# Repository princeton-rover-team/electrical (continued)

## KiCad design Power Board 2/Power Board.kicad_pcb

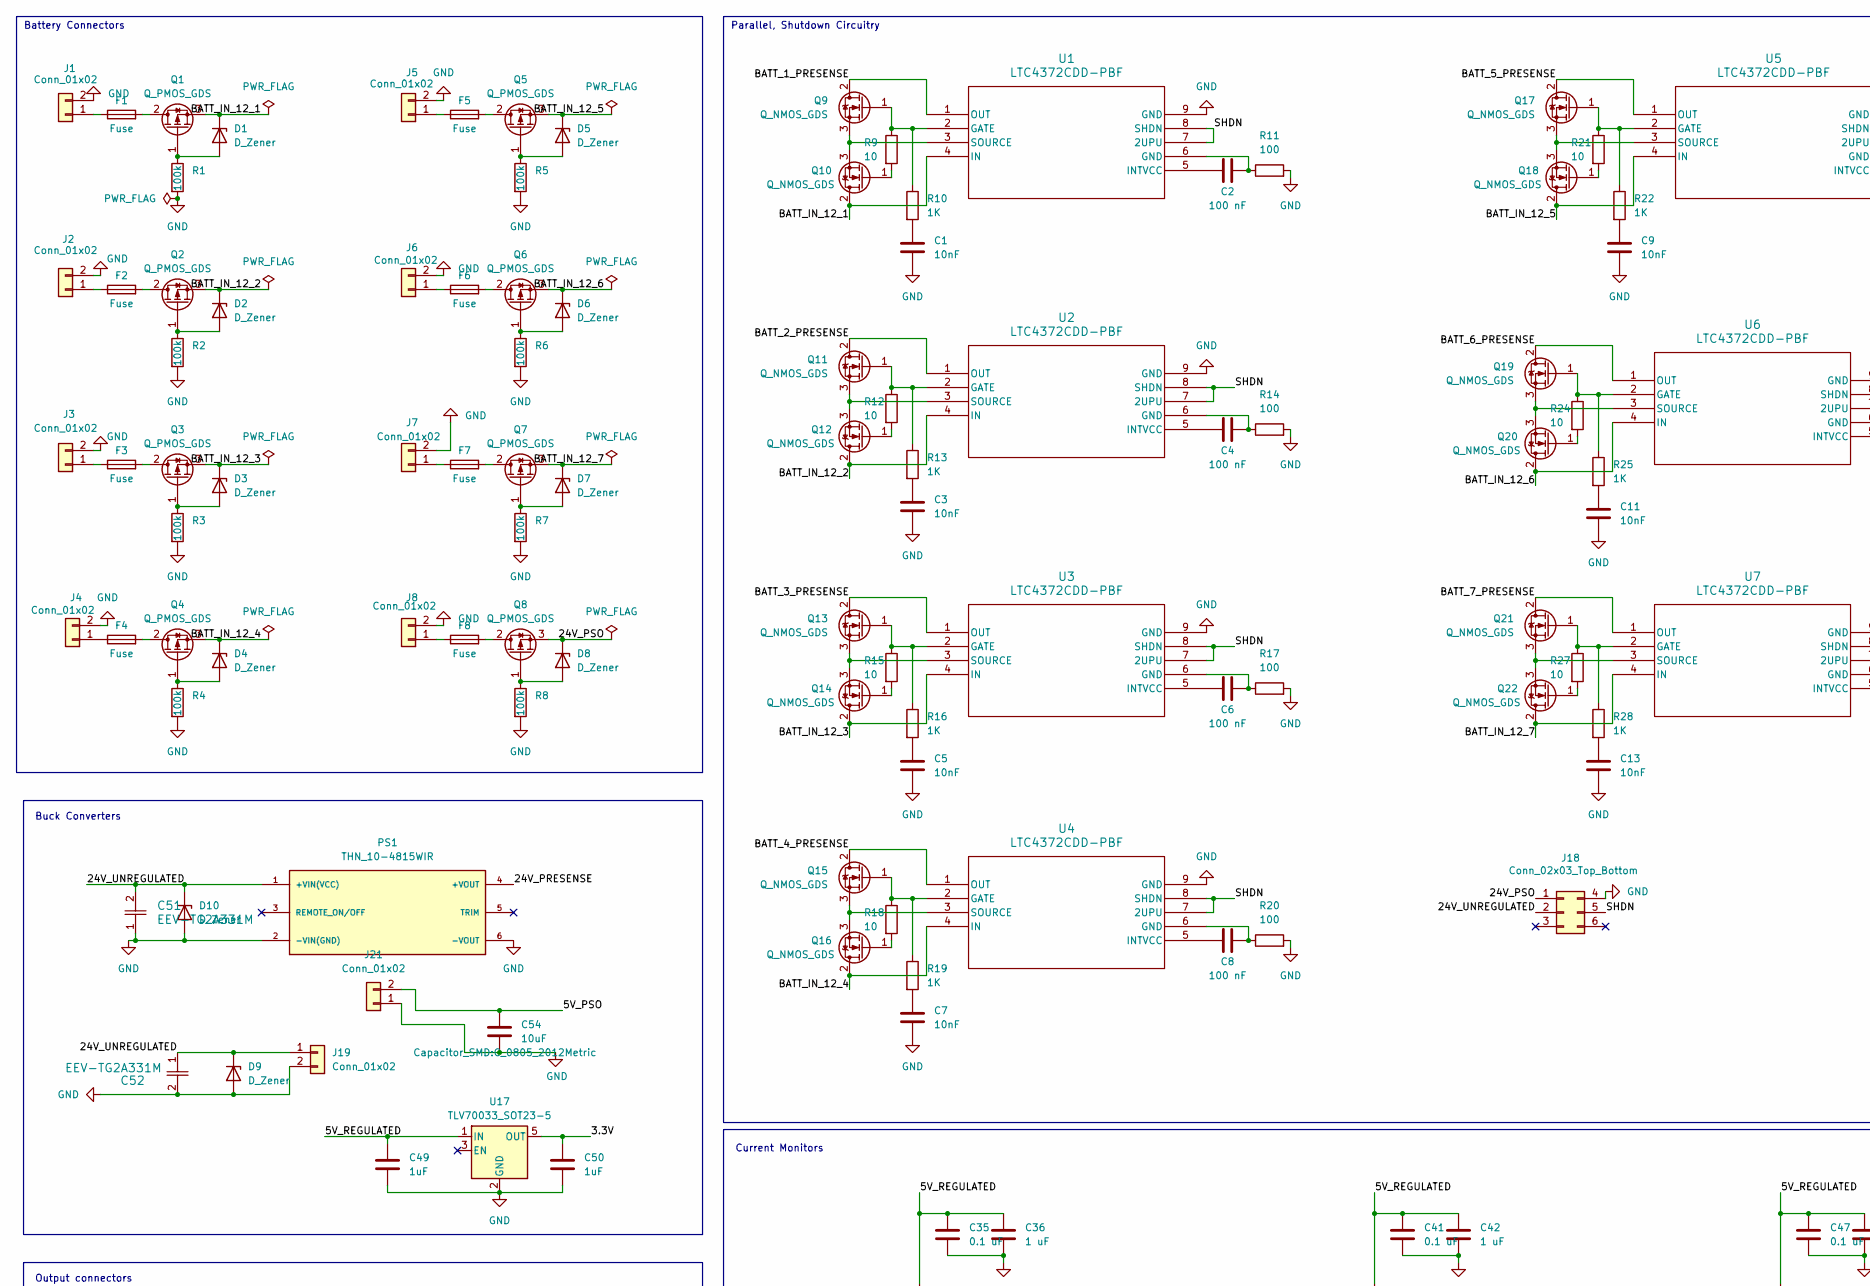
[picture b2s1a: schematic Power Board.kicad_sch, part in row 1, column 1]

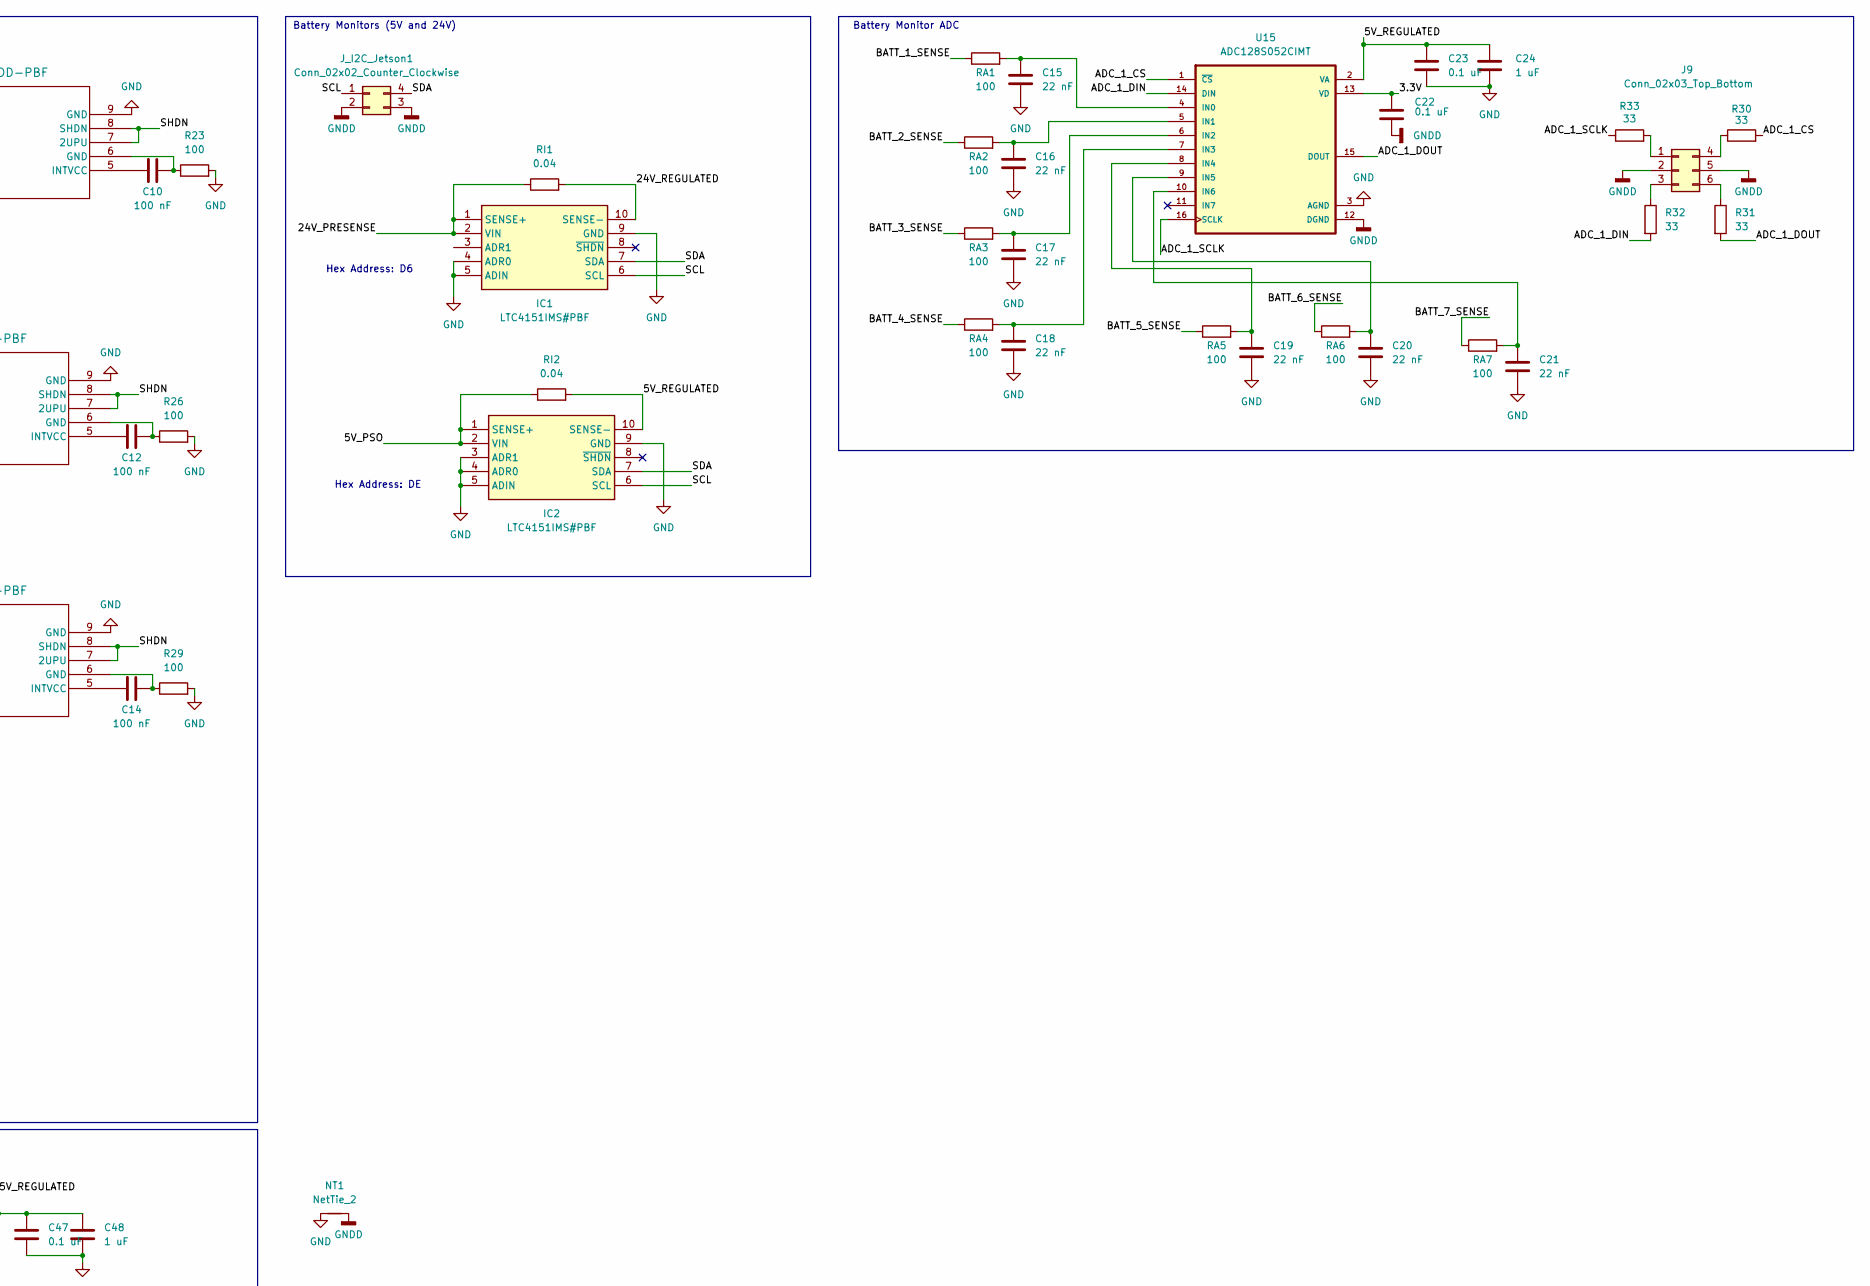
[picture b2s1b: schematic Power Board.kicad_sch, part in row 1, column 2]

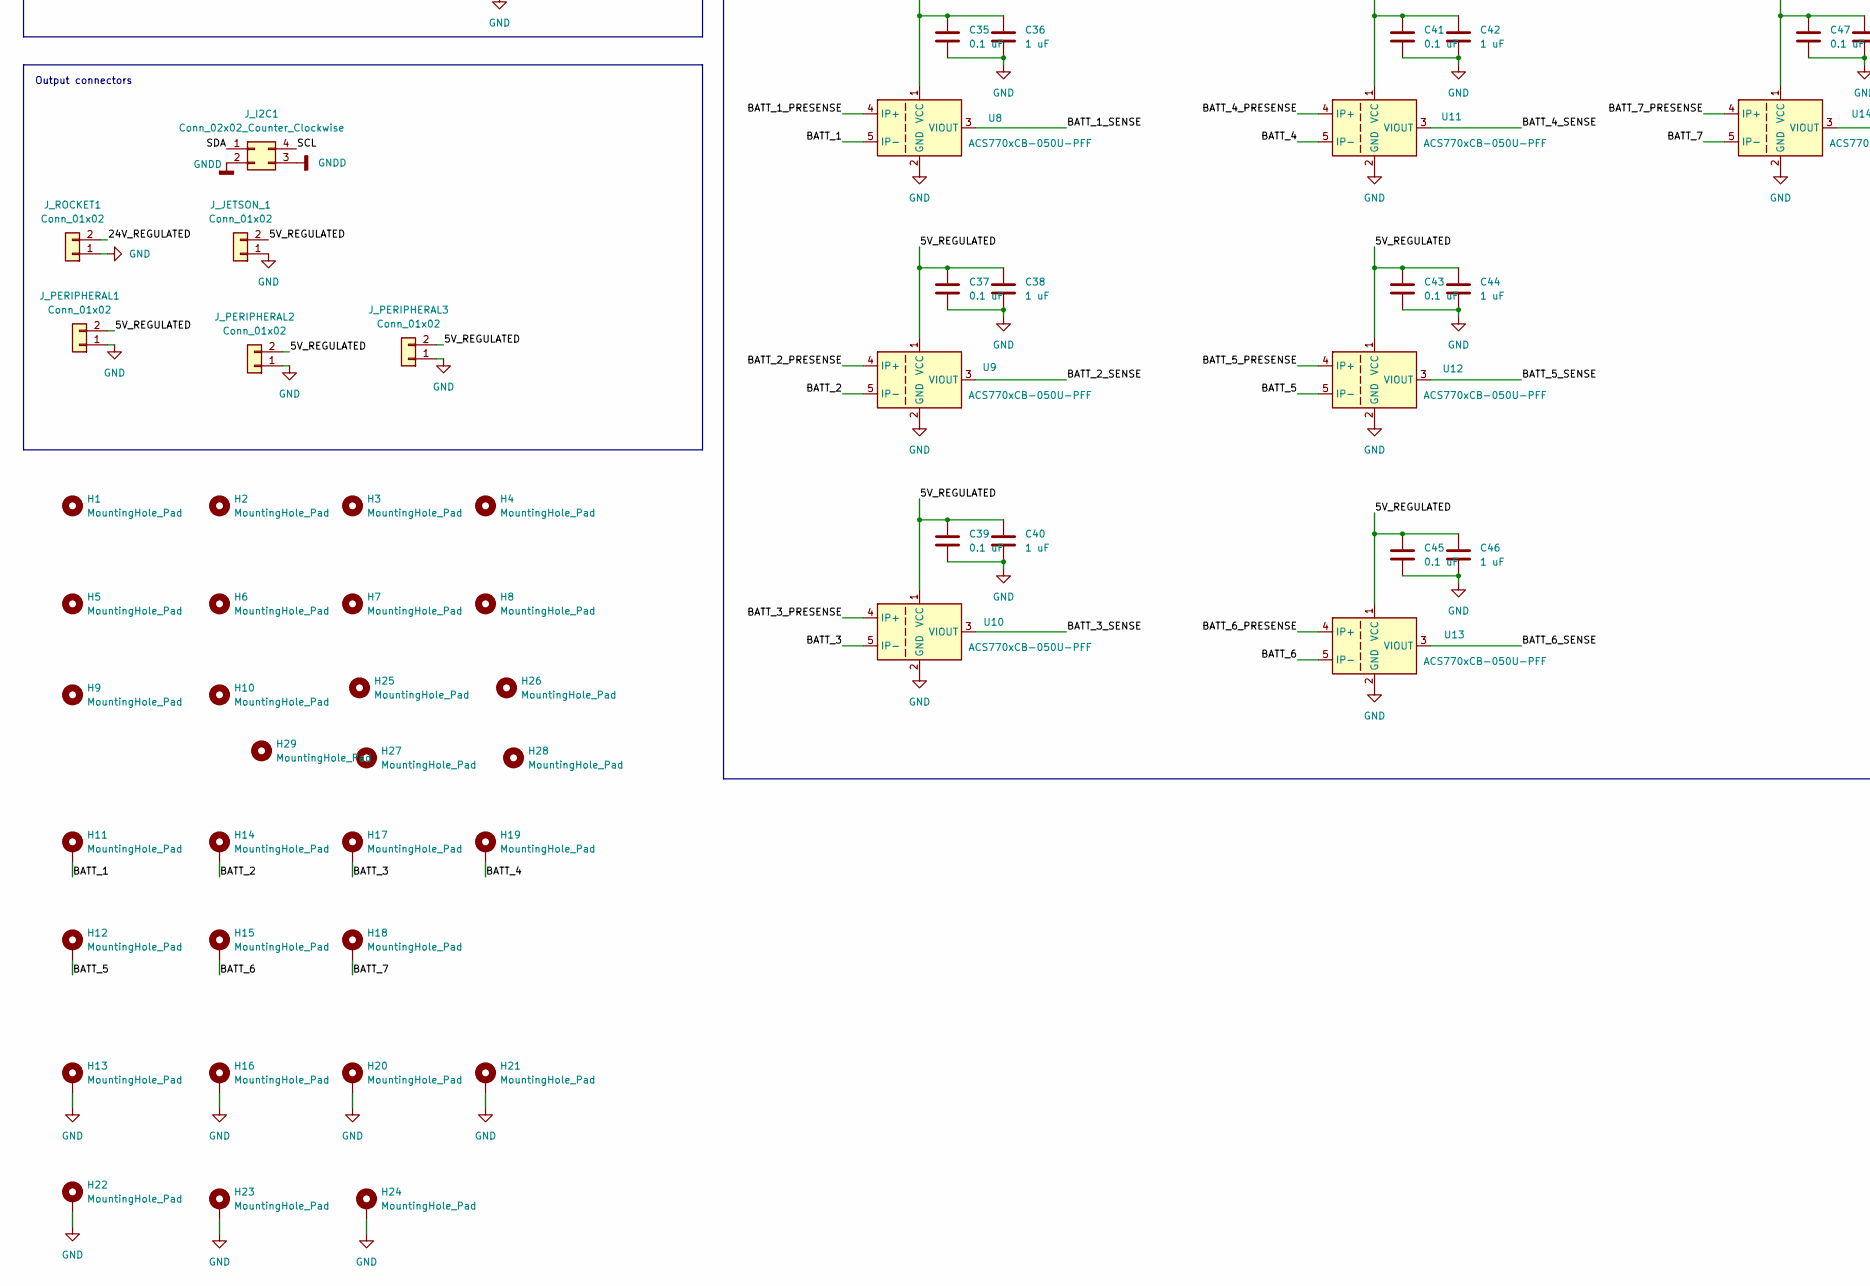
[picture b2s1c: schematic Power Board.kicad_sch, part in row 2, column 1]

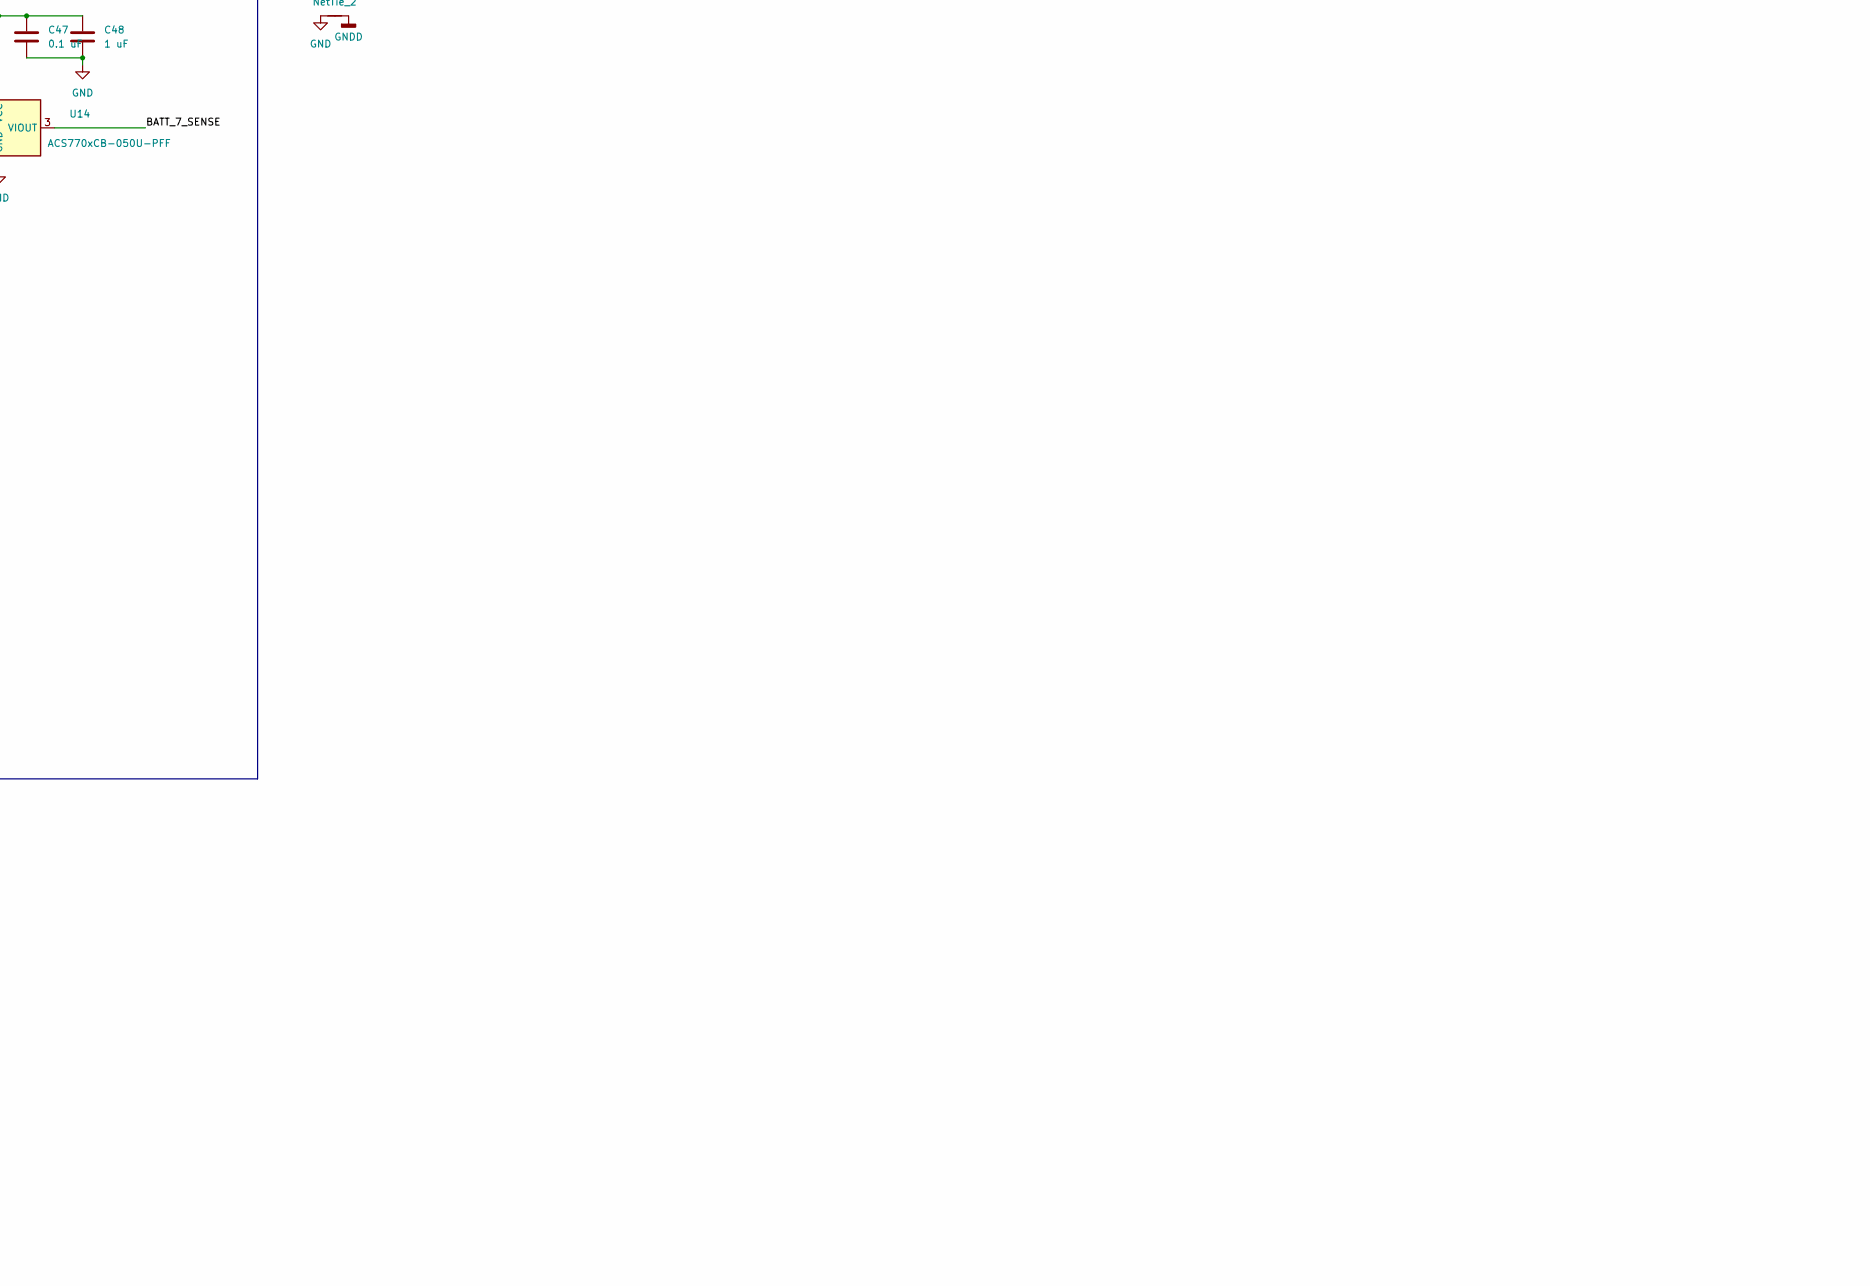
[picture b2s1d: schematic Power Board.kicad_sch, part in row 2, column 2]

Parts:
C1, C3, C5, C7, C9, C11, C13: 10nF; C_0603_1608Metric
C2, C4, C6, C8, C10, C12, C14: 100 nF; C_0603_1608Metric
C15, C16, C17, C18, C19, C20, C21: 22 nF; C_0603_1608Metric
C22, C23, C35, C37, C39, C41, C43, C45, C47: 0.1 uF; C_0603_1608Metric
C24, C36, C38, C40, C42, C44, C46, C48: 1 uF; C_0603_1608Metric
C49, C50: 1uF; C_0603_1608Metric
C51, C52: EEV-TG2A331M; CAP_SMD_19X19_PAN
C54: 10uF; C_0805_2012Metric
D1, D2, D3, D4, D5, D6, D7, D8: D_Zener; D_SOD-123; MANUFACTURER_PART_NUMBER BZT52C10-TP
D9, D10: D_Zener; D_SMB
F1, F2, F3, F4, F5, F6, F7, F8: Fuse; Fuse_0498060M
H1, H2, H3, H4, H5, H6, H7, H8, H9, H10, H25, H26, H27, H28, H29: MountingHole_Pad; MountingHole_3.2mm_M3_DIN965
H11, H12, H13, H14, H15, H16, H17, H18, H19, H20, H21, H22, H23, H24: MountingHole_Pad; MountingHole_4.3mm_M4_DIN965_Pad
IC1, IC2: LTC4151IMS#PBF; MSOP-10_3x3mm_P0.5mm; Mouser Part Number 584-LTC4151IMS#PBF
J1, J2, J3, J4, J5, J6, J7, J8: Conn_01x02; AMASS_XT60PW-F_1x02_P7.20mm_Horizontal; MANUFACTURER_PART_NUMBER 768290102
J9: Conn_02x03_Top_Bottom; Molex_Nano-Fit_105314-xx06_2x03_P2.50mm_Horizontal
J18: Conn_02x03_Top_Bottom; Molex_Nano-Fit_105310-xx06_2x03_P2.50mm_Vertical
J19, J21: Conn_01x02; TerminalBlock_WAGO_236-402_1x02_P5.00mm_45Degree
J_I2C1, J_I2C_Jetson1: Conn_02x02_Counter_Clockwise; Molex_Nano-Fit_105309-xx04_1x04_P2.50mm_Vertical
J_JETSON_1: Conn_01x02; AMASS_XT60-F_1x02_P7.20mm_Vertical
J_PERIPHERAL1, J_PERIPHERAL2, J_PERIPHERAL3: Conn_01x02; AMASS_XT60-F_1x02_P7.20mm_Vertical
J_ROCKET1: Conn_01x02; AMASS_XT60-F_1x02_P7.20mm_Vertical
NT1: NetTie_2
PS1: THN_10-4815WIR; CONV_THN_10-4815WIR; PARTREV Jan 27, 2021
Q1, Q2, Q3, Q4, Q5, Q6, Q7, Q8: Q_PMOS_GDS; PowerPAK_SO-8_Single
Q9, Q10, Q11, Q12, Q13, Q14, Q15, Q16, Q17, Q18, Q19, Q20, Q21, Q22: Q_NMOS_GDS; PowerPAK_SO-8_Single
R1, R2, R3, R4, R5, R6, R7, R8: 100k; R_0805_2012Metric_Pad1.20x1.40mm_HandSolder
R9, R12, R15, R18, R21, R24, R27: 10; R_0805_2012Metric_Pad1.20x1.40mm_HandSolder
R10, R13, R16, R19, R22, R25, R28: 1K; R_0805_2012Metric_Pad1.20x1.40mm_HandSolder
R11, R14, R17, R20, R23, R26, R29: 100; R_0805_2012Metric_Pad1.20x1.40mm_HandSolder
R30, R31, R32, R33: 33; R_0805_2012Metric_Pad1.20x1.40mm_HandSolder
RA1, RA2, RA3, RA4, RA5, RA6, RA7: 100; R_0805_2012Metric_Pad1.20x1.40mm_HandSolder
RI1, RI2: 0.04; R_0805_2012Metric_Pad1.20x1.40mm_HandSolder
U1, U2, U3, U4, U5, U6, U7: LTC4372CDD-PBF; 05-08-1698_ADI
U8, U9, U10, U11, U12, U13, U14: ACS770xCB-050U-PFF; Allegro_CB_PFF
U15: ADC128S052CIMT; SOP65P640X120-16N
U17: TLV70033_SOT23-5; SOT-23-5

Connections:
/3.3V: C22.1, C50.1, U15.13 (VD), U17.5 (OUT)
/5V_PSO: C54.1, IC2.1 (SENSE+), IC2.2 (VIN), J21.2, RI2.1
/5V_REGULATED: C23.1, C24.1, C35.1, C36.1, C37.1, C38.1, C39.1, C40.1, C41.1, C42.1, C43.1, C44.1, C45.1, C46.1, C47.1, C48.1, C49.1, IC2.10 (SENSE-), J_JETSON_1.2, J_PERIPHERAL1.2, J_PERIPHERAL2.2, J_PERIPHERAL3.2, RI2.2, U8.1 (VCC), U9.1 (VCC), U10.1 (VCC), U11.1 (VCC), U12.1 (VCC), U13.1 (VCC), U14.1 (VCC), U15.2 (VA), U17.1 (IN)
/24V_PRESENSE: IC1.1 (SENSE+), IC1.2 (VIN), PS1.4 (+VOUT), RI1.1
/24V_PSO: D8.1 (K), J18.1, Q8.3 (S)
/24V_REGULATED: IC1.10 (SENSE-), J_ROCKET1.2, RI1.2
/24V_UNREGULATED: C51.2, C52.1, D9.1 (K), D10.1 (K), J18.2, J19.1, PS1.1 (+VIN(VCC))
/ADC_1_CS: R30.2, U15.1 (~CS)
/ADC_1_DIN: R32.2, U15.14 (DIN)
/ADC_1_DOUT: R31.2, U15.15 (DOUT)
/ADC_1_SCLK: R33.1, U15.16 (SCLK)
/BATT_1: H11.1, U8.5 (IP-)
/BATT_1_PRESENSE: Q9.2 (D), U1.1 (OUT), U8.4 (IP+)
/BATT_1_SENSE: RA1.1, U8.3 (VIOUT)
/BATT_2: H14.1, U9.5 (IP-)
/BATT_2_PRESENSE: Q11.2 (D), U2.1 (OUT), U9.4 (IP+)
/BATT_2_SENSE: RA2.1, U9.3 (VIOUT)
/BATT_3: H17.1, U10.5 (IP-)
/BATT_3_PRESENSE: Q13.2 (D), U3.1 (OUT), U10.4 (IP+)
/BATT_3_SENSE: RA3.1, U10.3 (VIOUT)
/BATT_4: H19.1, U11.5 (IP-)
/BATT_4_PRESENSE: Q15.2 (D), U4.1 (OUT), U11.4 (IP+)
/BATT_4_SENSE: RA4.1, U11.3 (VIOUT)
/BATT_5: H12.1, U12.5 (IP-)
/BATT_5_PRESENSE: Q17.2 (D), U5.1 (OUT), U12.4 (IP+)
/BATT_5_SENSE: RA5.1, U12.3 (VIOUT)
/BATT_6: H15.1, U13.5 (IP-)
/BATT_6_PRESENSE: Q19.2 (D), U6.1 (OUT), U13.4 (IP+)
/BATT_6_SENSE: RA6.1, U13.3 (VIOUT)
/BATT_7: H18.1, U14.5 (IP-)
/BATT_7_PRESENSE: Q21.2 (D), U7.1 (OUT), U14.4 (IP+)
/BATT_7_SENSE: RA7.1, U14.3 (VIOUT)
/BATT_IN_12_1: D1.1 (K), Q1.3 (S), Q10.2 (D), U1.4 (IN)
/BATT_IN_12_2: D2.1 (K), Q2.3 (S), Q12.2 (D), U2.4 (IN)
/BATT_IN_12_3: D3.1 (K), Q3.3 (S), Q14.2 (D), U3.4 (IN)
/BATT_IN_12_4: D4.1 (K), Q4.3 (S), Q16.2 (D), U4.4 (IN)
/BATT_IN_12_5: D5.1 (K), Q5.3 (S), Q18.2 (D), U5.4 (IN)
/BATT_IN_12_6: D6.1 (K), Q6.3 (S), Q20.2 (D), U6.4 (IN)
/BATT_IN_12_7: D7.1 (K), Q7.3 (S), Q22.2 (D), U7.4 (IN)
/SCL: IC1.6 (SCL), IC2.6 (SCL), J_I2C1.4, J_I2C_Jetson1.1
/SDA: IC1.7 (SDA), IC2.7 (SDA), J_I2C1.1, J_I2C_Jetson1.4
/SHDN: J18.5, U1.7 (2UPU), U1.8 (SHDN), U2.7 (2UPU), U2.8 (SHDN), U3.7 (2UPU), U3.8 (SHDN), U4.7 (2UPU), U4.8 (SHDN), U5.7 (2UPU), U5.8 (SHDN), U6.7 (2UPU), U6.8 (SHDN), U7.7 (2UPU), U7.8 (SHDN)
GND: C1.2, C3.2, C5.2, C7.2, C9.2, C11.2, C13.2, C15.2, C16.2, C17.2, C18.2, C19.2, C20.2, C21.2, C23.2, C24.2, C35.2, C36.2, C37.2, C38.2, C39.2, C40.2, C41.2, C42.2, C43.2, C44.2, C45.2, C46.2, C47.2, C48.2, C49.2, C50.2, C51.1, C52.2, C54.2, D9.2 (A), D10.2 (A), H13.1, H16.1, H20.1, H21.1, H22.1, H23.1, H24.1, IC1.4 (ADR0), IC1.5 (ADIN), IC1.9 (GND), IC2.3 (ADR1), IC2.4 (ADR0), IC2.5 (ADIN), IC2.9 (GND), J1.2, J2.2, J3.2, J4.2, J5.2, J6.2, J7.2, J8.2, J18.4, J19.2, J21.1, J_JETSON_1.1, J_PERIPHERAL1.1, J_PERIPHERAL2.1, J_PERIPHERAL3.1, J_ROCKET1.1, PS1.2 (-VIN(GND)), PS1.6 (-VOUT), R1.2, R2.2, R3.2, R4.2, R5.2, R6.2, R7.2, R8.2, R11.2, R14.2, R17.2, R20.2, R23.2, R26.2, R29.2, U1.9 (GND), U2.9 (GND), U3.9 (GND), U4.9 (GND), U5.9 (GND), U6.9 (GND), U7.9 (GND), U8.2 (GND), U9.2 (GND), U10.2 (GND), U11.2 (GND), U12.2 (GND), U13.2 (GND), U14.2 (GND), U15.3 (AGND), U17.2 (GND)
GNDD: C22.2, J9.2, J9.5, J_I2C1.2, J_I2C1.3, J_I2C_Jetson1.2, J_I2C_Jetson1.3, NT1.2, U2.12, U15.12 (DGND)
unnamed: C1.1, R10.2
unnamed: C2.1, R11.1, U1.6 (GND)
unnamed: C3.1, R13.2
unnamed: C4.1, R14.1, U2.6 (GND)
unnamed: C5.1, R16.2
unnamed: C6.1, R17.1, U3.6 (GND)
unnamed: C7.1, R19.2
unnamed: C8.1, R20.1, U4.6 (GND)
unnamed: C9.1, R22.2
unnamed: C10.1, R23.1, U5.6 (GND)
unnamed: C11.1, R25.2
unnamed: C12.1, R26.1, U6.6 (GND)
unnamed: C13.1, R28.2
unnamed: C14.1, R29.1, U7.6 (GND)
unnamed: D1.2 (A), Q1.1 (G), R1.1
unnamed: D2.2 (A), Q2.1 (G), R2.1
unnamed: D3.2 (A), Q3.1 (G), R3.1
unnamed: D4.2 (A), Q4.1 (G), R4.1
unnamed: D5.2 (A), Q5.1 (G), R5.1
unnamed: D6.2 (A), Q6.1 (G), R6.1
unnamed: D7.2 (A), Q7.1 (G), R7.1
unnamed: D8.2 (A), Q8.1 (G), R8.1
unnamed: F1.1, J1.1
unnamed: F2.1, J2.1
unnamed: F3.1, J3.1
unnamed: F4.1, J4.1
unnamed: F5.1, J5.1
unnamed: F6.1, J6.1
unnamed: F7.1, J7.1
unnamed: F8.1, J8.1
unnamed: J9.1, R33.2
unnamed: J9.3, R32.1
unnamed: J9.4, R30.1
unnamed: J9.6, R31.1
unnamed: F1.2, Q1.2 (D)
unnamed: F2.2, Q2.2 (D)
unnamed: F3.2, Q3.2 (D)
unnamed: F4.2, Q4.2 (D)
unnamed: F5.2, Q5.2 (D)
unnamed: F6.2, Q6.2 (D)
unnamed: F7.2, Q7.2 (D)
unnamed: F8.2, Q8.2 (D)
unnamed: Q9.1 (G), R9.1, R10.1, U1.2 (GATE)
unnamed: Q10.1 (G), R9.2
unnamed: Q9.3 (S), Q10.3 (S), U1.3 (SOURCE)
unnamed: Q11.1 (G), R12.1, R13.1, U2.2 (GATE)
unnamed: Q11.3 (S), Q12.3 (S), U2.3 (SOURCE)
unnamed: Q12.1 (G), R12.2
unnamed: Q13.1 (G), R15.1, R16.1, U3.2 (GATE)
unnamed: Q13.3 (S), Q14.3 (S), U3.3 (SOURCE)
unnamed: Q14.1 (G), R15.2
unnamed: Q15.1 (G), R18.1, R19.1, U4.2 (GATE)
unnamed: Q15.3 (S), Q16.3 (S), U4.3 (SOURCE)
unnamed: Q16.1 (G), R18.2
unnamed: Q17.1 (G), R21.1, R22.1, U5.2 (GATE)
unnamed: Q17.3 (S), Q18.3 (S), U5.3 (SOURCE)
unnamed: Q18.1 (G), R21.2
unnamed: Q19.1 (G), R24.1, R25.1, U6.2 (GATE)
unnamed: Q19.3 (S), Q20.3 (S), U6.3 (SOURCE)
unnamed: Q20.1 (G), R24.2
unnamed: Q21.1 (G), R27.1, R28.1, U7.2 (GATE)
unnamed: Q21.3 (S), Q22.3 (S), U7.3 (SOURCE)
unnamed: Q22.1 (G), R27.2
unnamed: C2.2, U1.5 (INTVCC)
unnamed: C4.2, U2.5 (INTVCC)
unnamed: C6.2, U3.5 (INTVCC)
unnamed: C8.2, U4.5 (INTVCC)
unnamed: C10.2, U5.5 (INTVCC)
unnamed: C12.2, U6.5 (INTVCC)
unnamed: C14.2, U7.5 (INTVCC)
unnamed: C15.1, RA1.2, U15.4 (IN0)
unnamed: C16.1, RA2.2, U15.5 (IN1)
unnamed: C17.1, RA3.2, U15.6 (IN2)
unnamed: C18.1, RA4.2, U15.7 (IN3)
unnamed: C19.1, RA5.2, U15.8 (IN4)
unnamed: C20.1, RA6.2, U15.9 (IN5)
unnamed: C21.1, RA7.2, U15.10 (IN6)

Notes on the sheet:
Battery Monitors (5V and 24V)
Parallel, Shutdown Circuitry
Battery Connectors
Buck Converters
Current Monitors
Output connectors
Battery Monitor ADC
Hex Address: D6
Hex Address: DE

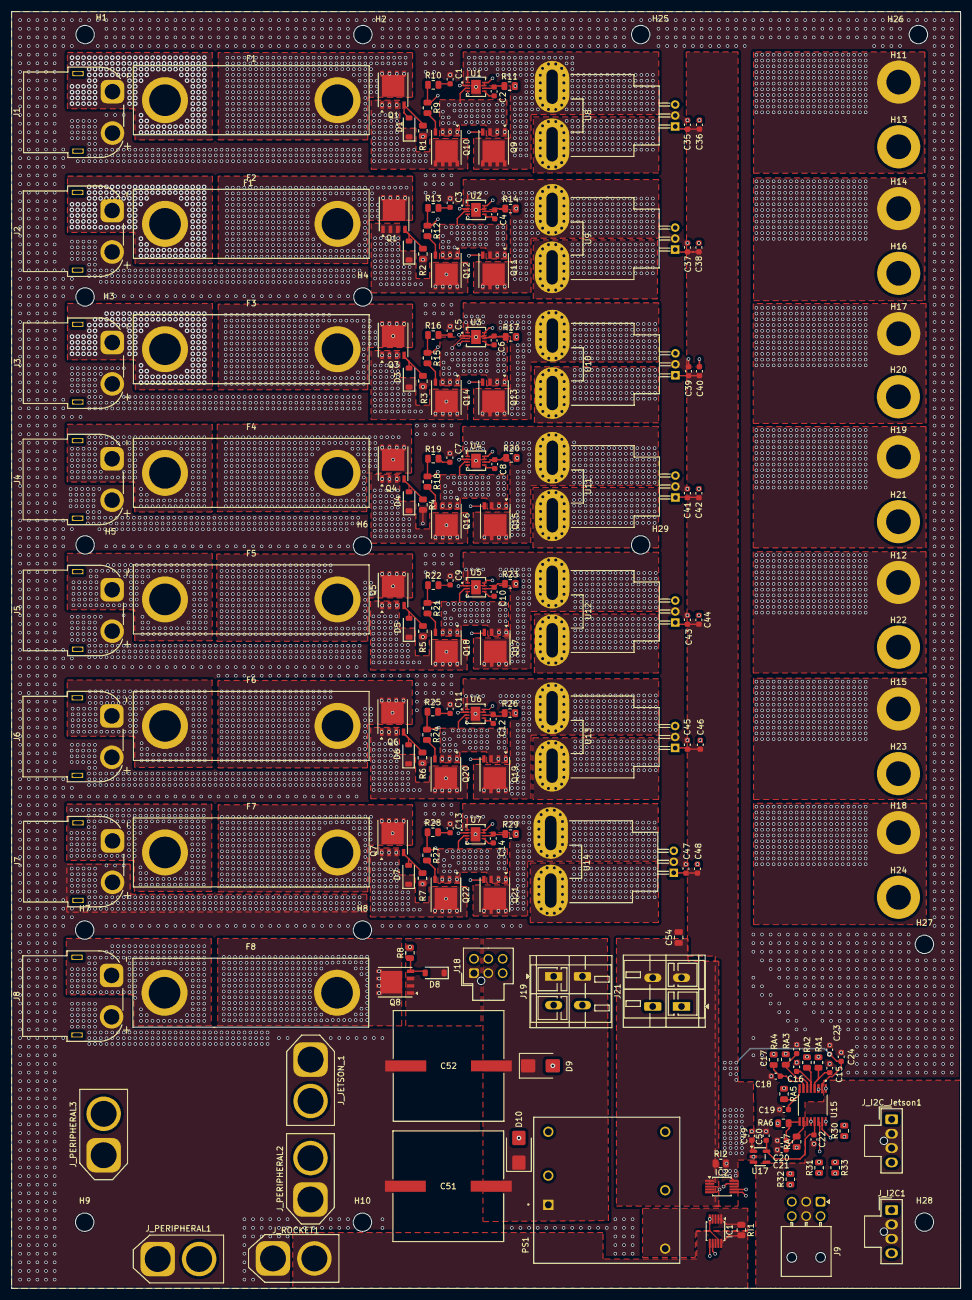
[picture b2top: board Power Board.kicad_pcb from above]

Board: 4 copper layers, 165.0 x 222.0 mm, 192 parts (0 on the bottom side), 121 nets.

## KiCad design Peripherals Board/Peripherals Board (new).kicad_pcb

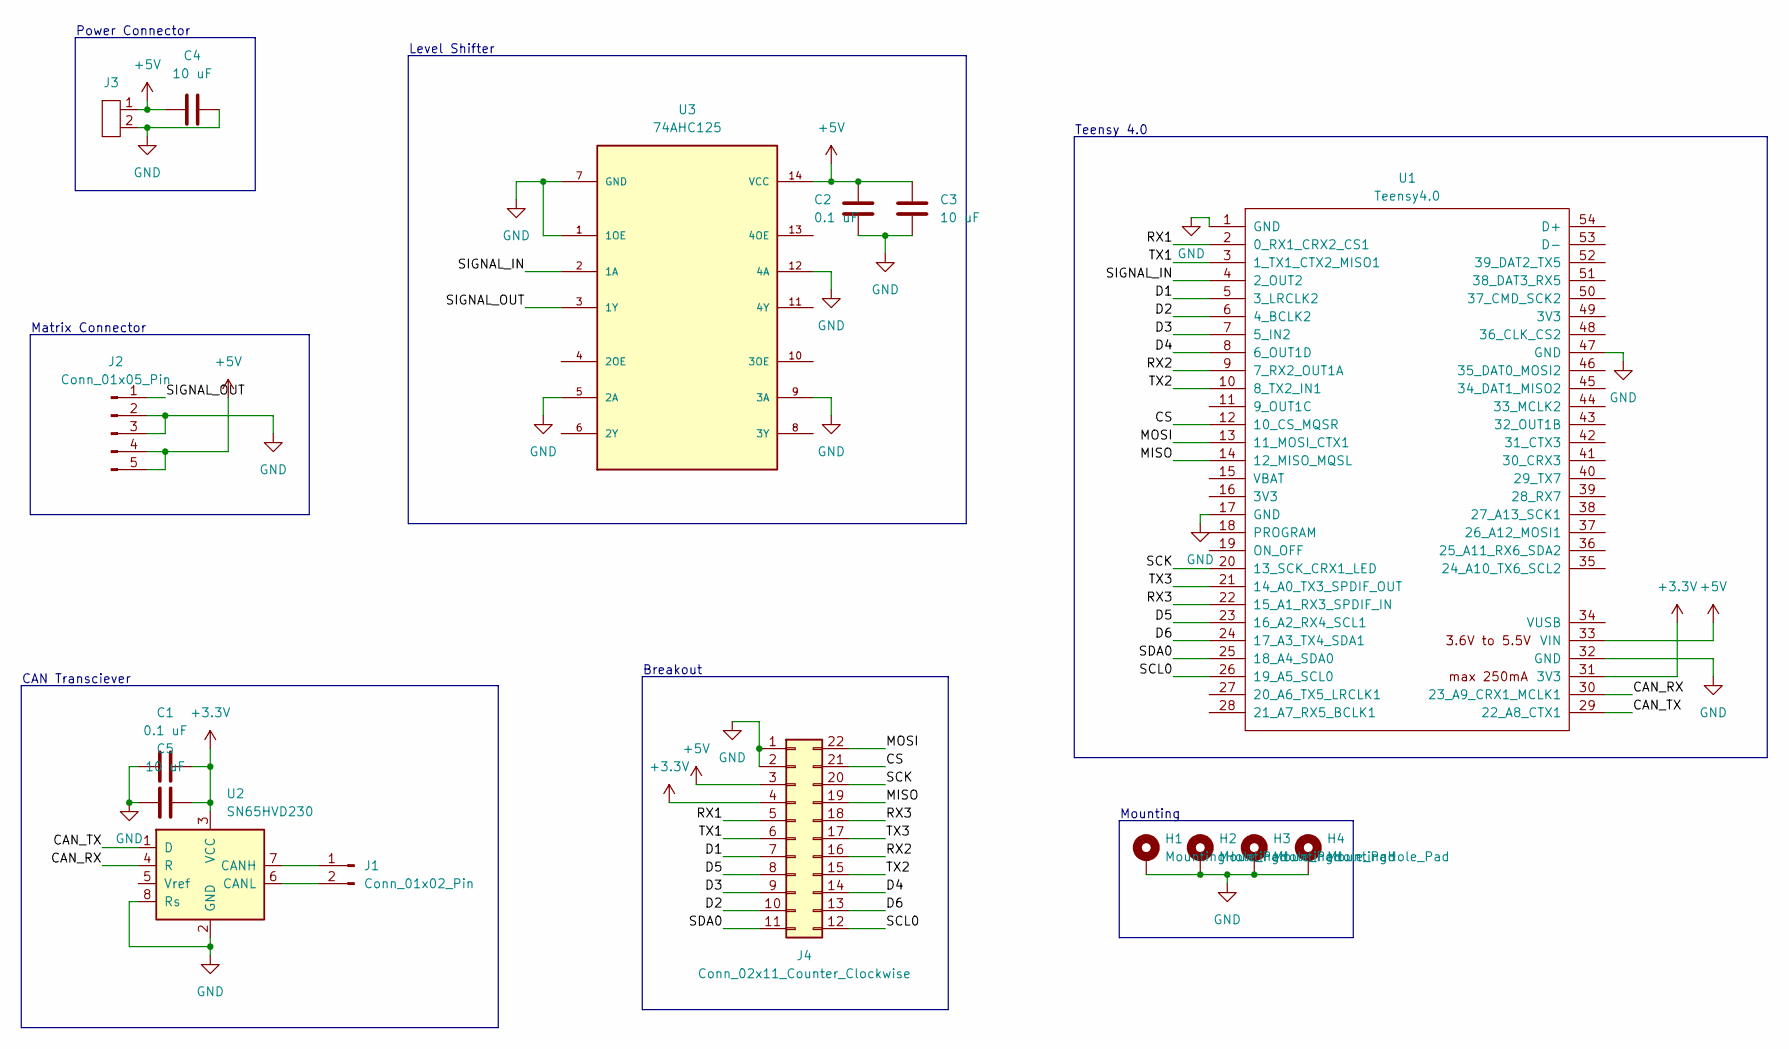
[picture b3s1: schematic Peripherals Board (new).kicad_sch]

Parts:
C1, C2: 0.1 uF; C_0805_2012Metric
C3, C4, C5: 10 uF; C_0805_2012Metric
H1, H2, H3, H4: MountingHole_Pad; MountingHole_2.2mm_M2_Pad
J1: Conn_01x02_Pin; JST_GH_BM02B-GHS-TBT_1x02-1MP_P1.25mm_Vertical
J2: Conn_01x05_Pin; JST_GH_BM05B-GHS-TBT_1x05-1MP_P1.25mm_Vertical
J3: XT30PW-M
J4: Conn_02x11_Counter_Clockwise; PinSocket_2x11_P2.54mm_Vertical
U1: Teensy4.0; Teensy40
U2: SN65HVD230; SOIC-8_3.9x4.9mm_P1.27mm
U3: 74AHC125; SO-14_3.9x8.65mm_P1.27mm

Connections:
+3.3V: C1.1, C5.2, J4.4, U1.31 (3V3), U2.3 (VCC)
+5V: C2.1, C3.1, C4.2, J2.4, J2.5, J3.1 (A), J4.3, U1.33 (VIN), U3.14 (VCC)
/CAN_RX: U1.30 (23_A9_CRX1_MCLK1), U2.4 (R)
/CAN_TX: U1.29 (22_A8_CTX1), U2.1 (D)
/CS: J4.21, U1.12 (10_CS_MQSR)
/D1: J4.7, U1.5 (3_LRCLK2)
/D2: J4.10, U1.6 (4_BCLK2)
/D3: J4.9, U1.7 (5_IN2)
/D4: J4.14, U1.8 (6_OUT1D)
/D5: J4.8, U1.23 (16_A2_RX4_SCL1)
/D6: J4.13, U1.24 (17_A3_TX4_SDA1)
/MISO: J4.19, U1.14 (12_MISO_MQSL)
/MOSI: J4.22, U1.13 (11_MOSI_CTX1)
/RX1: J4.5, U1.2 (0_RX1_CRX2_CS1)
/RX2: J4.16, U1.9 (7_RX2_OUT1A)
/RX3: J4.18, U1.22 (15_A1_RX3_SPDIF_IN)
/SCK: J4.20, U1.20 (13_SCK_CRX1_LED)
/SCL0: J4.12, U1.26 (19_A5_SCL0)
/SDA0: J4.11, U1.25 (18_A4_SDA0)
/SIGNAL_IN: U1.4 (2_OUT2), U3.2 (1A)
/SIGNAL_OUT: J2.1, U3.3 (1Y)
/TX1: J4.6, U1.3 (1_TX1_CTX2_MISO1)
/TX2: J4.15, U1.10 (8_TX2_IN1)
/TX3: J4.17, U1.21 (14_A0_TX3_SPDIF_OUT)
GND: C1.2, C2.2, C3.2, C4.1, C5.1, H1.1, H2.1, H3.1, H4.1, J2.2, J2.3, J3.2 (B), J4.1, J4.2, U1.1 (GND), U1.17 (GND), U1.32 (GND), U1.47 (GND), U2.2 (GND), U2.8 (Rs), U3.1 (1OE), U3.5 (2A), U3.7 (GND), U3.9 (3A), U3.12 (4A)
unnamed: J1.1, U2.7 (CANH)
unnamed: J1.2, U2.6 (CANL)

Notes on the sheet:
CAN Transciever
Level Shifter
Matrix Connector
Power Connector
Teensy 4.0
Mounting
Breakout

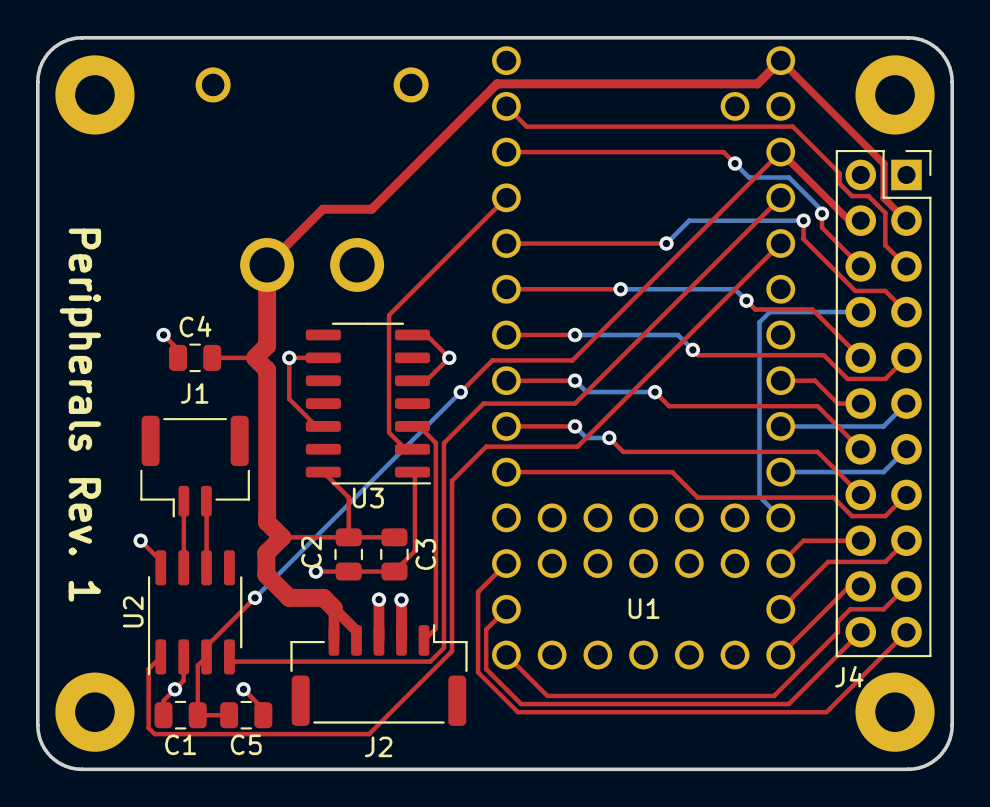
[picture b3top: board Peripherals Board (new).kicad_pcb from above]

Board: 2 copper layers, 50.8 x 40.6 mm, 16 parts (0 on the bottom side), 27 nets.

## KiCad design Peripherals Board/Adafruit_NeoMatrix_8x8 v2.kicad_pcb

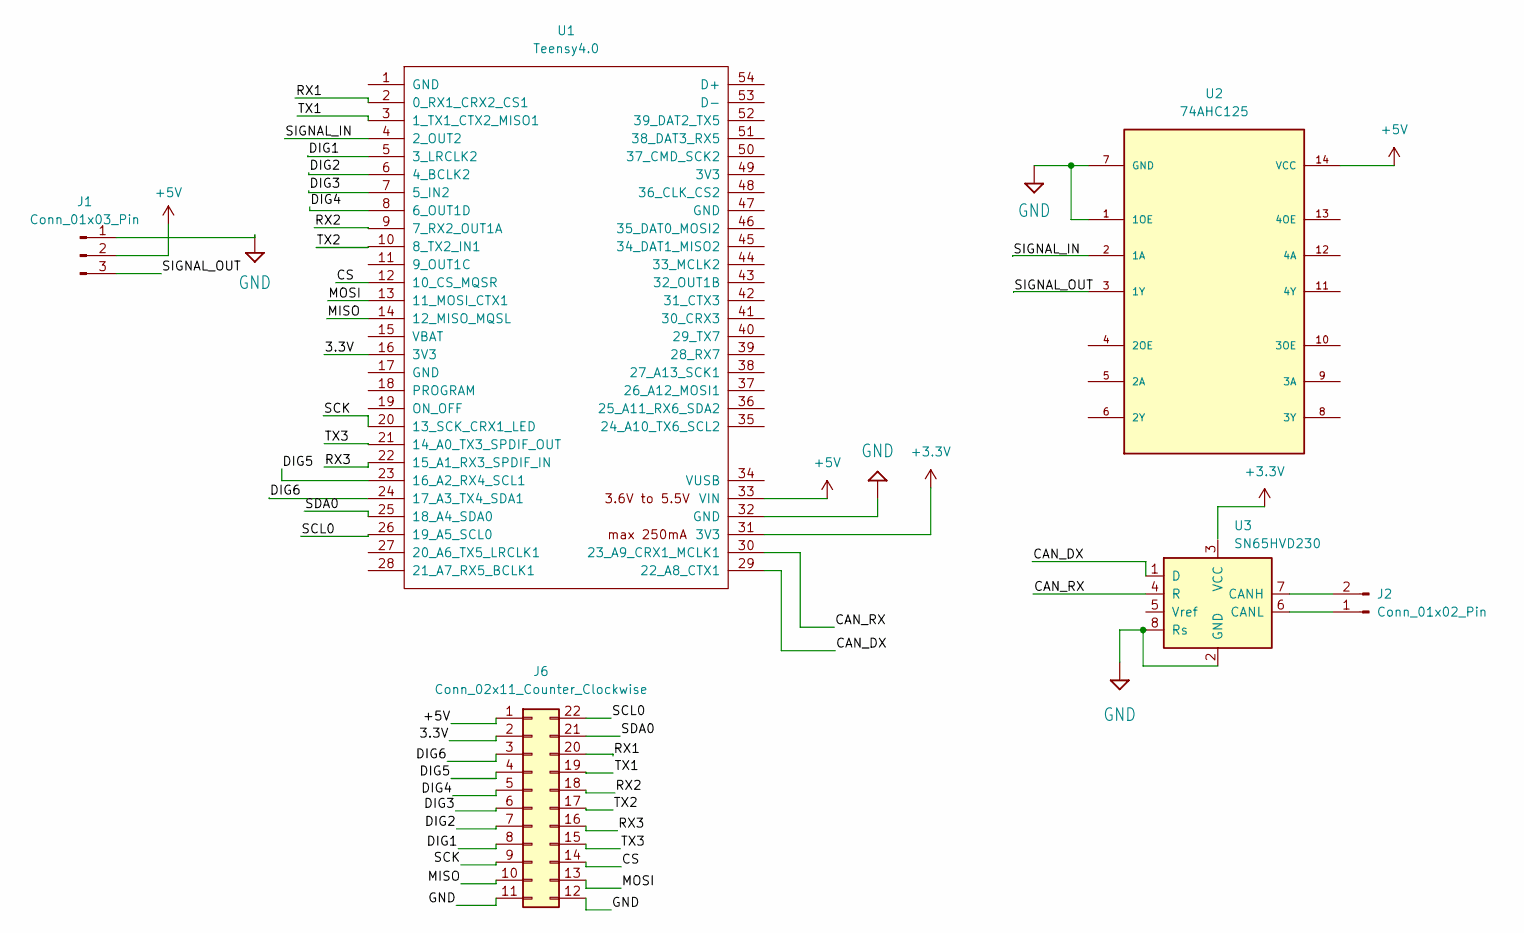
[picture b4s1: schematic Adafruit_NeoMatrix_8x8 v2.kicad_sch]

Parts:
J1: Conn_01x03_Pin; JST_GH_SM03B-GHS-TB_1x03-1MP_P1.25mm_Horizontal
J2: Conn_01x02_Pin; JST_GH_SM02B-GHS-TB_1x02-1MP_P1.25mm_Horizontal
J6: Conn_02x11_Counter_Clockwise; PinSocket_2x11_P2.54mm_Vertical
U1: Teensy4.0; Teensy40
U2: 74AHC125; 14DIP
U3: SN65HVD230; SOIC-8_3.9x4.9mm_P1.27mm

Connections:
+3.3V: U1.31 (3V3)
+5V: J1.2, J6.1, U1.33 (VIN), U2.14 (VCC)
/3.3V: J6.2, U1.16 (3V3)
/CAN_DX: U1.29 (22_A8_CTX1), U3.1 (D)
/CAN_RX: U1.30 (23_A9_CRX1_MCLK1), U3.4 (R)
/CS: J6.14, U1.12 (10_CS_MQSR)
/DIG1: J6.8, U1.5 (3_LRCLK2)
/DIG2: J6.7, U1.6 (4_BCLK2)
/DIG3: J6.6, U1.7 (5_IN2)
/DIG4: J6.5, U1.8 (6_OUT1D)
/DIG5: J6.4, U1.23 (16_A2_RX4_SCL1)
/DIG6: J6.3
/MISO: J6.10, U1.14 (12_MISO_MQSL)
/MOSI: J6.13, U1.13 (11_MOSI_CTX1)
/RX1: J6.20, U1.2 (0_RX1_CRX2_CS1)
/RX2: J6.18, U1.9 (7_RX2_OUT1A)
/RX3: J6.16, U1.22 (15_A1_RX3_SPDIF_IN)
/SCK: J6.9, U1.20 (13_SCK_CRX1_LED)
/SCL0: J6.22, U1.26 (19_A5_SCL0)
/SDA0: J6.21, U1.25 (18_A4_SDA0)
/SIGNAL_IN: U1.4 (2_OUT2), U2.2 (1A)
/SIGNAL_OUT: J1.3, U2.3 (1Y)
/TX1: U1.3 (1_TX1_CTX2_MISO1)
/TX2: J6.17, U1.10 (8_TX2_IN1)
/TX3: J6.15, U1.21 (14_A0_TX3_SPDIF_OUT)
GND: J1.1, J6.11, J6.12, U1.32 (GND), U2.1 (1OE), U2.7 (GND), U3.2 (GND), U3.8 (Rs)
unnamed: J2.1, U3.6 (CANL)
unnamed: J2.2, U3.7 (CANH)

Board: 2 copper layers, 6 parts (0 on the bottom side), 25 nets, no tracks yet.

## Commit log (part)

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2023-10-30 Added peripherals board
2023-11-05 Add footprints and layouts
2023-11-09 organized peripherals board schematic
2023-11-09 initialized power board
2023-11-12 replace corrupted schematic file
2023-11-12 Added CAN Bus software folder
2023-11-12 Got CAN transmission working between 2 teensy 4.0s
2024-01-31 remade peripherals board
2024-01-31 minor changes
2024-01-31 gerbers
2024-02-04 initialized peripherals firmware
2024-02-04 added CAN example
2024-02-07 Worked more on peripherals board code
2024-02-18 Updated power board schematic and libraries
2024-02-18 feat: schematic for 8-channel single-ended ADC + symlib
2024-02-18 Worked on gas gauge
2024-03-24 working on power board
2025-11-02 power board update
2025-11-06 updated resistor values
2025-11-07 added resistor and capacitor footprints
2025-11-07 libraries update
2025-11-16 connectors update
2025-11-21 separated current sensors and updated ADCs, component numbering
2025-12-03 updated schematic numbering, made rough PCB design for battery 1
2025-12-03 adc design on power board
2026-01-18 laid out most components, reworked battery 1 pours, made connections for ADCs; buck converter layout and routing in progress
2026-01-21 changed ADC connectors, added series resistors
2026-01-23 updated LTC4372s, switch connector, ADC; added some power planes for other batteries
2026-01-24 more layout, power planes for 24V and 5V rails, current sensing and switch connections; might move digital section with ADCs and LTC4151s to bottom left
2026-01-28 Added the beginnings of the BMS schematic (the only parts in the schematic right now are JST-XH connectors and one chip). Added libraries for the battery monitoring/balancing chip: BQ76942
2026-02-05 aaryan jagtap
2026-02-05 removed thermistors and ADC; conserved space
2026-02-08 updated layout and pours
2026-02-08 updated xt60 connectors, routed ADC lines
2026-02-09 i2c routing
2026-02-12 moved bms stuff out of power board folder
2026-02-12 Delete Power Board/BMS Board directory
    moved out of the power board folder
2026-02-14 more pin configs for bq chip
2026-02-14 Delete BMS Board directory
    to resolve a merge conflict
2026-02-15 added M3 mounting holes, removed buck converter (to be replaced with half-brick), added more pours
2026-02-22 added XT60 connectors for 5V rail and standoffs for BMS, 5V converter
2026-02-26 pours battery presense
2026-02-26 pours battery
2026-02-27 minor tracing updates for batteries on PDB
2026-03-14 added some via stitching on pcb, to be completed
2026-03-14 new power board folder because github sucks
2026-03-14 more via stitching
2026-03-19 pours and vias for battery outputs
2026-03-20 screw terminals for 5V buck, pour + stitching
2026-03-22 changed mounting holes to without pad for star grounding
2026-04-23 power board minor changes
2026-05-18 via stitching on power board
2026-05-18 BMS schematic with individual monitoring ICs + I2C MUX
2026-05-18 started pcb layout for BMS board
2026-05-18 BMS layout for three batteries done
2026-05-19 BMS pretty much completed
2026-05-19 BMS completed + via stitching
2026-05-19 added LED to monitor 5v power
2026-05-19 added mounting holes
2026-05-28 minor updates to BMS; edge cuts, GND pour, via stitching, missed connections for PDB
